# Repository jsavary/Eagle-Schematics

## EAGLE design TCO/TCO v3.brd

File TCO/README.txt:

/************/
*  TCO v1    *
/************/

for roco solenoide turnout with DCC input voltage

/************/
*  TCO v2    *
/************/

some new idea

/************/
*  TCO v3    *
/************/

for Xpressnet tco with arduino
see more at : https://github.com/nzin/xpressnet_arduino

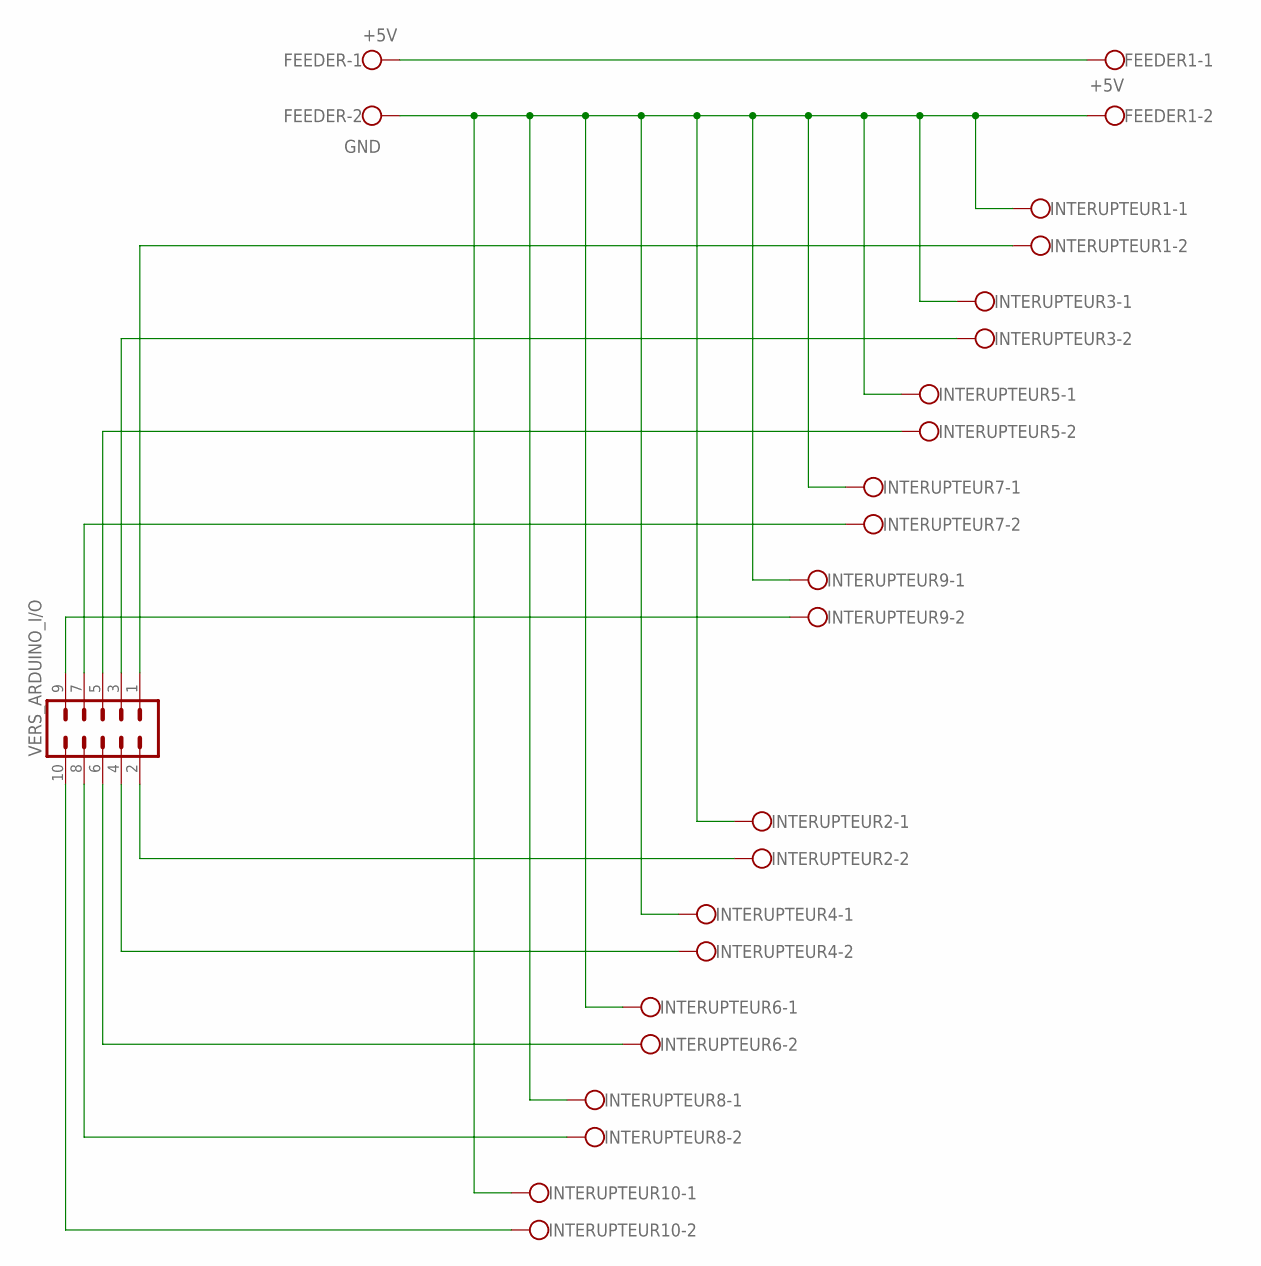
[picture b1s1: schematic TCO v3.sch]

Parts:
FEEDER, FEEDER1: W237-102
INTERUPTEUR1, INTERUPTEUR2, INTERUPTEUR3, INTERUPTEUR4, INTERUPTEUR5, INTERUPTEUR6, INTERUPTEUR7, INTERUPTEUR8, INTERUPTEUR9, INTERUPTEUR10: W237-102
VERS_ARDUINO_I/O: MA05-2

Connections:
unnamed: FEEDER.1, FEEDER1.1
unnamed: INTERUPTEUR1.2, VERS_ARDUINO_I/O.1
unnamed: INTERUPTEUR3.2, VERS_ARDUINO_I/O.3
unnamed: INTERUPTEUR5.2, VERS_ARDUINO_I/O.5
unnamed: INTERUPTEUR7.2, VERS_ARDUINO_I/O.7
unnamed: INTERUPTEUR9.2, VERS_ARDUINO_I/O.9
unnamed: INTERUPTEUR2.2, VERS_ARDUINO_I/O.2
unnamed: INTERUPTEUR4.2, VERS_ARDUINO_I/O.4
unnamed: INTERUPTEUR6.2, VERS_ARDUINO_I/O.6
unnamed: INTERUPTEUR8.2, VERS_ARDUINO_I/O.8
unnamed: INTERUPTEUR10.2, VERS_ARDUINO_I/O.10
unnamed: FEEDER.2, FEEDER1.2, INTERUPTEUR1.1, INTERUPTEUR2.1, INTERUPTEUR3.1, INTERUPTEUR4.1, INTERUPTEUR5.1, INTERUPTEUR6.1, INTERUPTEUR7.1, INTERUPTEUR8.1, INTERUPTEUR9.1, INTERUPTEUR10.1

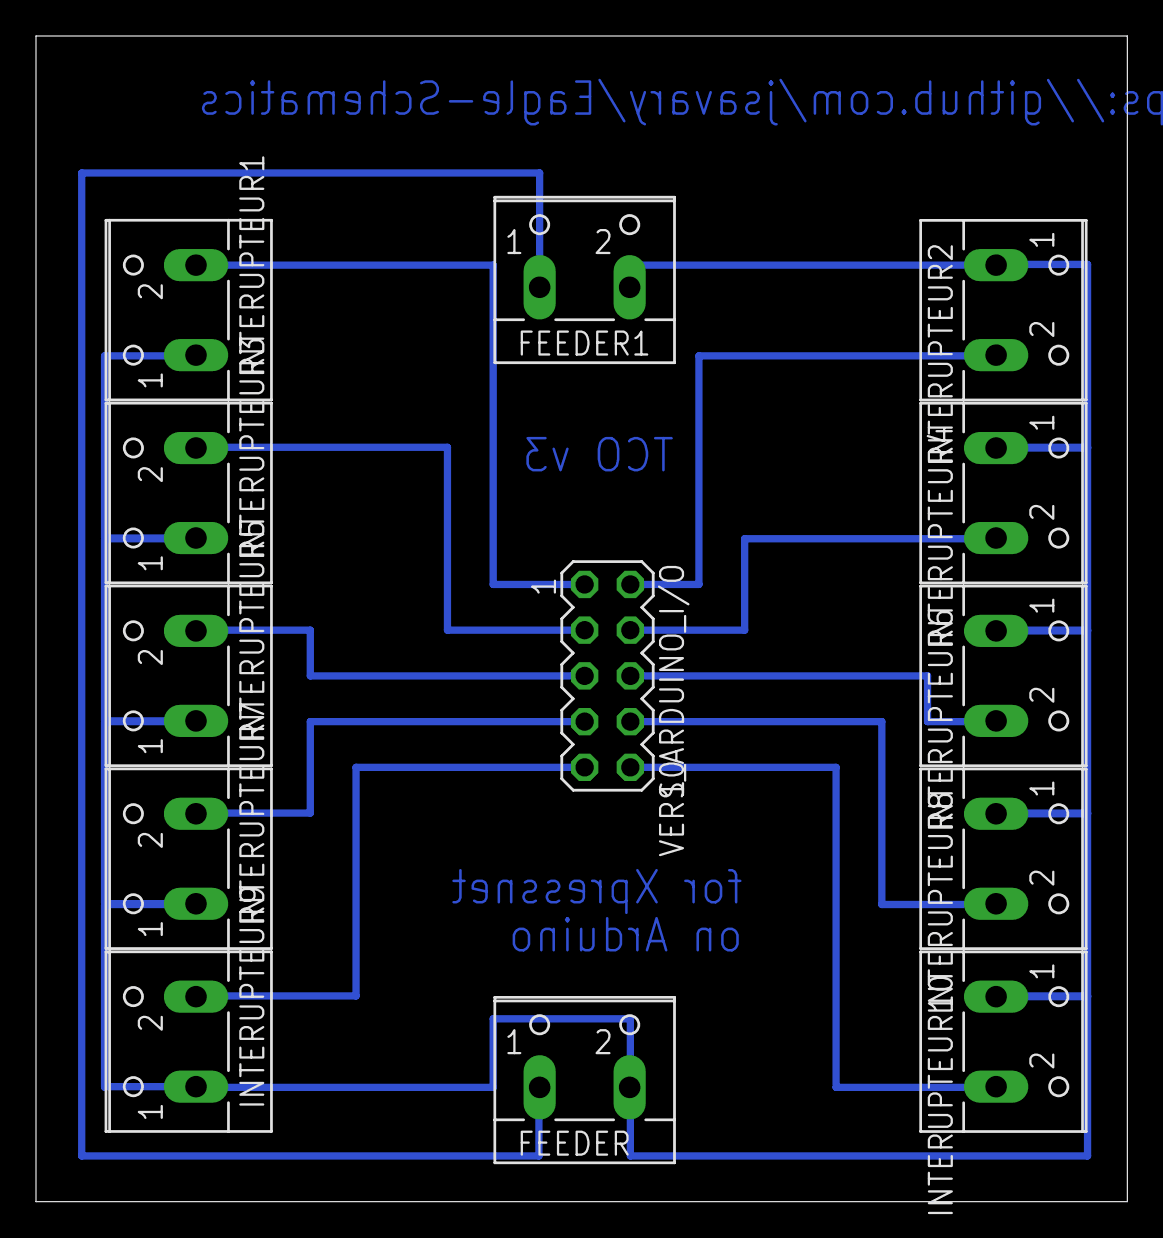
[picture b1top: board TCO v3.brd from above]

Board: 2 copper layers, 60.6 x 64.8 mm, 13 parts (0 on the bottom side), 12 nets.

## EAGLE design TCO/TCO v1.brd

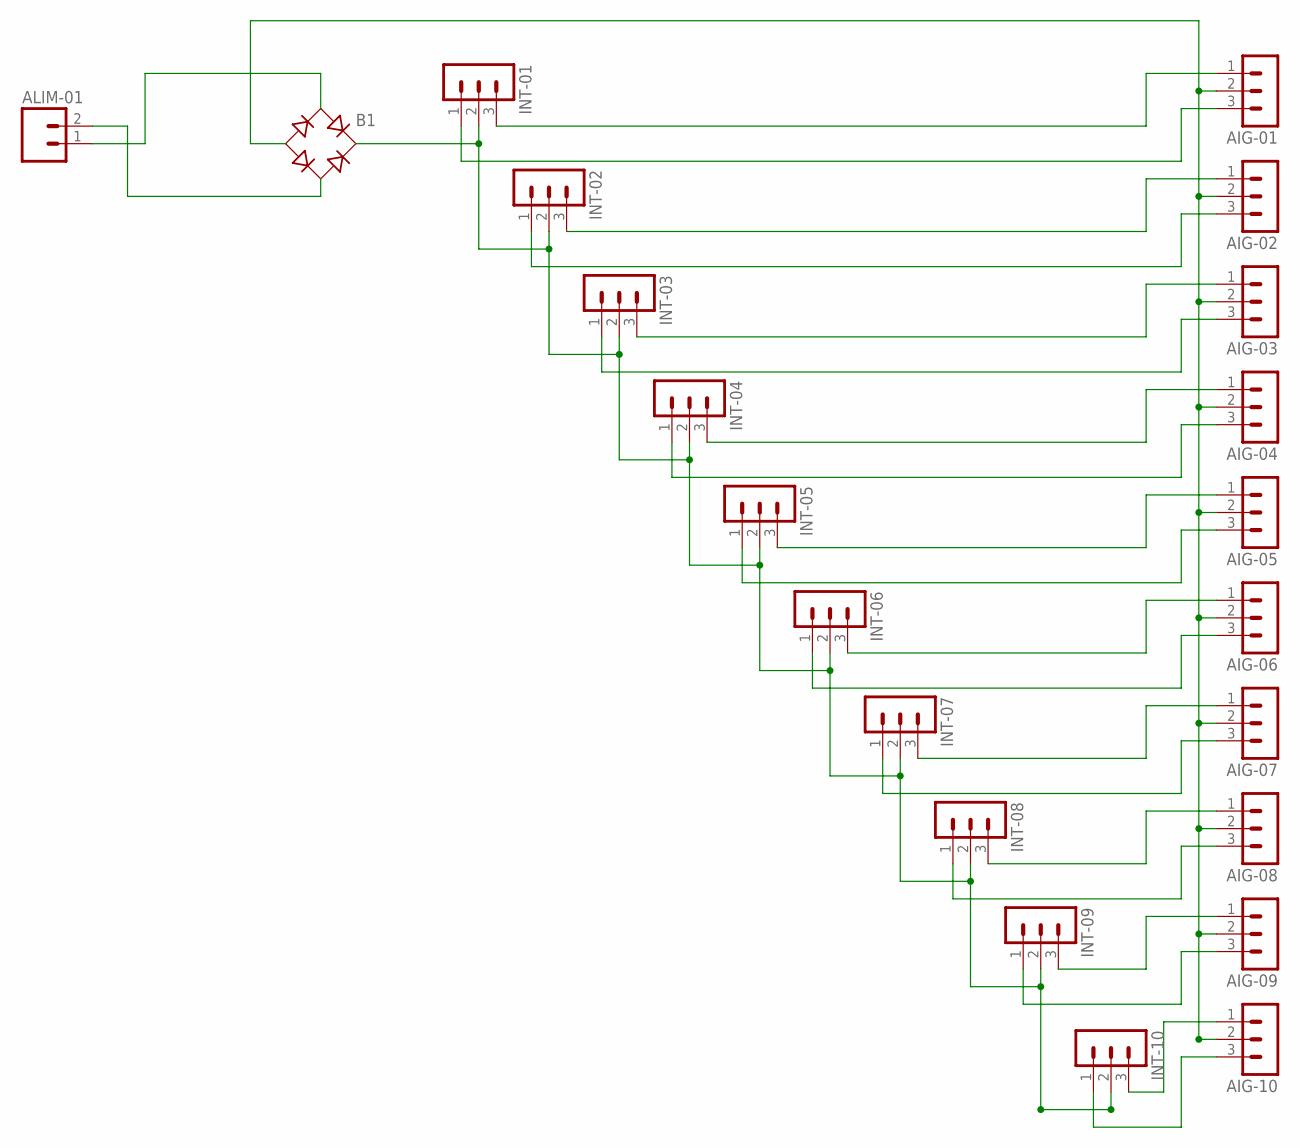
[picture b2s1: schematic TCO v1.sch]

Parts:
AIG-01, AIG-02, AIG-03, AIG-04, AIG-05, AIG-06, AIG-07, AIG-08, AIG-09, AIG-10: MA03-1
ALIM-01: M02; 02P
B1: B-DIL
INT-01, INT-02, INT-03, INT-04, INT-05, INT-06, INT-07, INT-08, INT-09, INT-10: MA03-1

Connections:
unnamed: ALIM-01.1, B1.AC1
unnamed: AIG-01.2, AIG-02.2, AIG-03.2, AIG-04.2, AIG-05.2, AIG-06.2, AIG-07.2, AIG-08.2, AIG-09.2, AIG-10.2, B1.-
unnamed: AIG-01.3, INT-01.1
unnamed: B1.+, INT-01.2, INT-02.2, INT-03.2, INT-04.2, INT-05.2, INT-06.2, INT-07.2, INT-08.2, INT-09.2, INT-10.2
unnamed: AIG-01.1, INT-01.3
unnamed: AIG-02.3, INT-02.1
unnamed: AIG-02.1, INT-02.3
unnamed: AIG-03.3, INT-03.1
unnamed: AIG-03.1, INT-03.3
unnamed: AIG-04.3, INT-04.1
unnamed: AIG-04.1, INT-04.3
unnamed: AIG-05.1, INT-05.3
unnamed: AIG-05.3, INT-05.1
unnamed: AIG-06.1, INT-06.3
unnamed: AIG-06.3, INT-06.1
unnamed: AIG-07.1, INT-07.3
unnamed: AIG-07.3, INT-07.1
unnamed: AIG-08.1, INT-08.3
unnamed: AIG-08.3, INT-08.1
unnamed: AIG-09.1, INT-09.3
unnamed: AIG-09.3, INT-09.1
unnamed: AIG-10.1, INT-10.3
unnamed: AIG-10.3, INT-10.1
unnamed: ALIM-01.2, B1.AC2

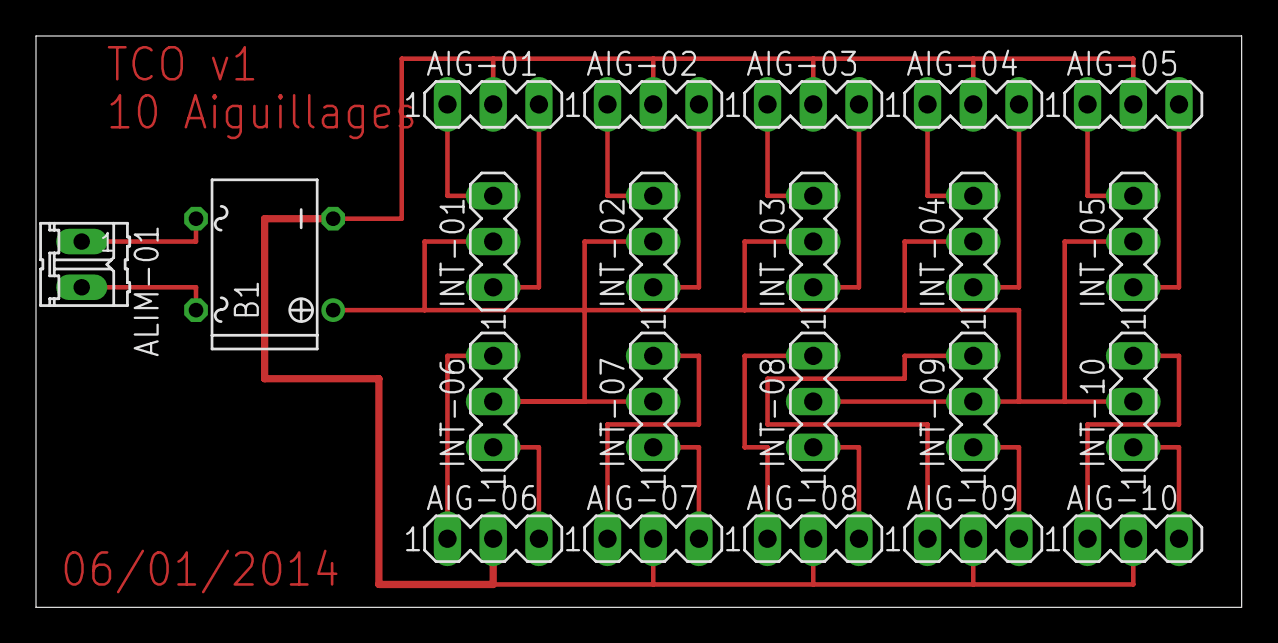
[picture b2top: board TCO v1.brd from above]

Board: 2 copper layers, 67.0 x 31.7 mm, 22 parts (0 on the bottom side), 24 nets.

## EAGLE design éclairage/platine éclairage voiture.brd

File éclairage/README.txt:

/**********************/
* Light cabine for DCC *
/**********************/

This is Made for light into the cabine of trains.

enjoy!

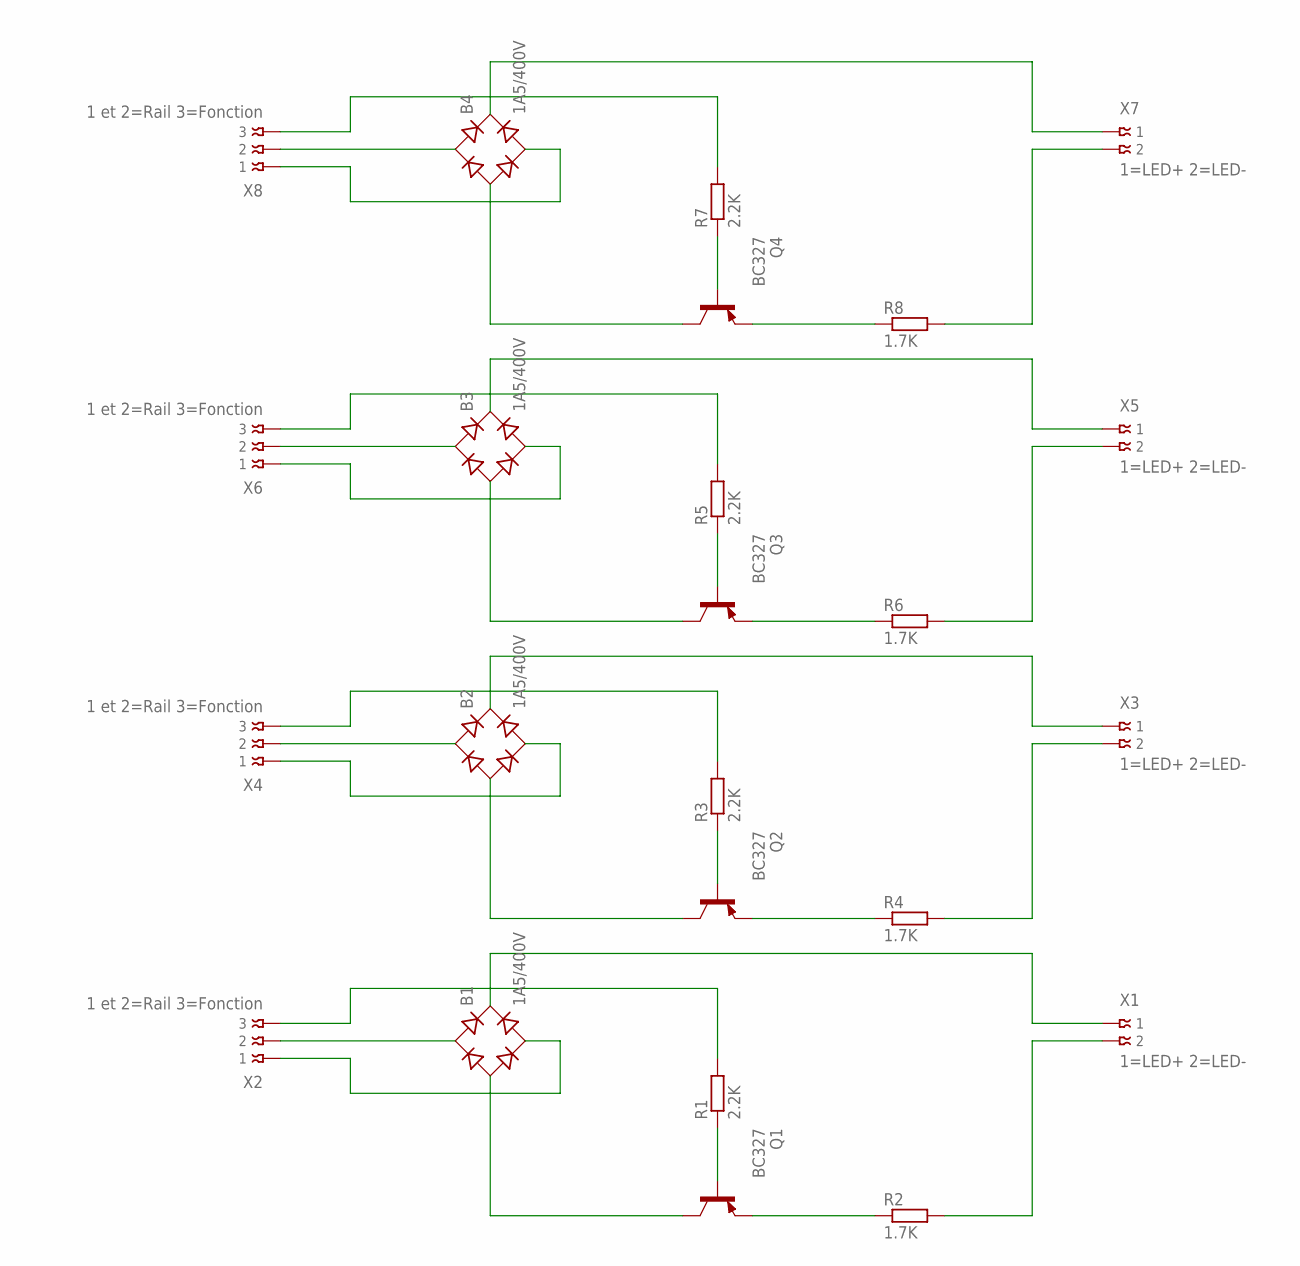
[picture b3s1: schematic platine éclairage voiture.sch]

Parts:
B1, B2, B3, B4: 1A5/400V; RB1A
Q1, Q2, Q3, Q4: BC327; TO92-EBC
R1, R3, R5, R7: 2.2K; 0207/10
R2, R4, R6, R8: 1.7K; 0207/10
X1, X3, X5, X7: 1=LED+ 2=LED-; 009176002
X2, X4, X6, X8: 1 et 2=Rail 3=Fonction; 009176003

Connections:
unnamed: B1.-, Q1.C
unnamed: Q1.B, R1.1
unnamed: R1.2, X2.3
unnamed: Q1.E, R2.1
unnamed: R2.2, X1.2
unnamed: B1.+, X1.1
unnamed: B1.AC1, X2.2
unnamed: B1.AC2, X2.1
unnamed: B2.-, Q2.C
unnamed: Q2.B, R3.1
unnamed: R3.2, X4.3
unnamed: Q2.E, R4.1
unnamed: R4.2, X3.2
unnamed: B2.+, X3.1
unnamed: B2.AC1, X4.2
unnamed: B2.AC2, X4.1
unnamed: B3.-, Q3.C
unnamed: Q3.B, R5.1
unnamed: R5.2, X6.3
unnamed: Q3.E, R6.1
unnamed: R6.2, X5.2
unnamed: B3.+, X5.1
unnamed: B3.AC2, X6.1
unnamed: B3.AC1, X6.2
unnamed: B4.-, Q4.C
unnamed: Q4.B, R7.1
unnamed: R7.2, X8.3
unnamed: Q4.E, R8.1
unnamed: R8.2, X7.2
unnamed: B4.+, X7.1
unnamed: B4.AC2, X8.1
unnamed: B4.AC1, X8.2

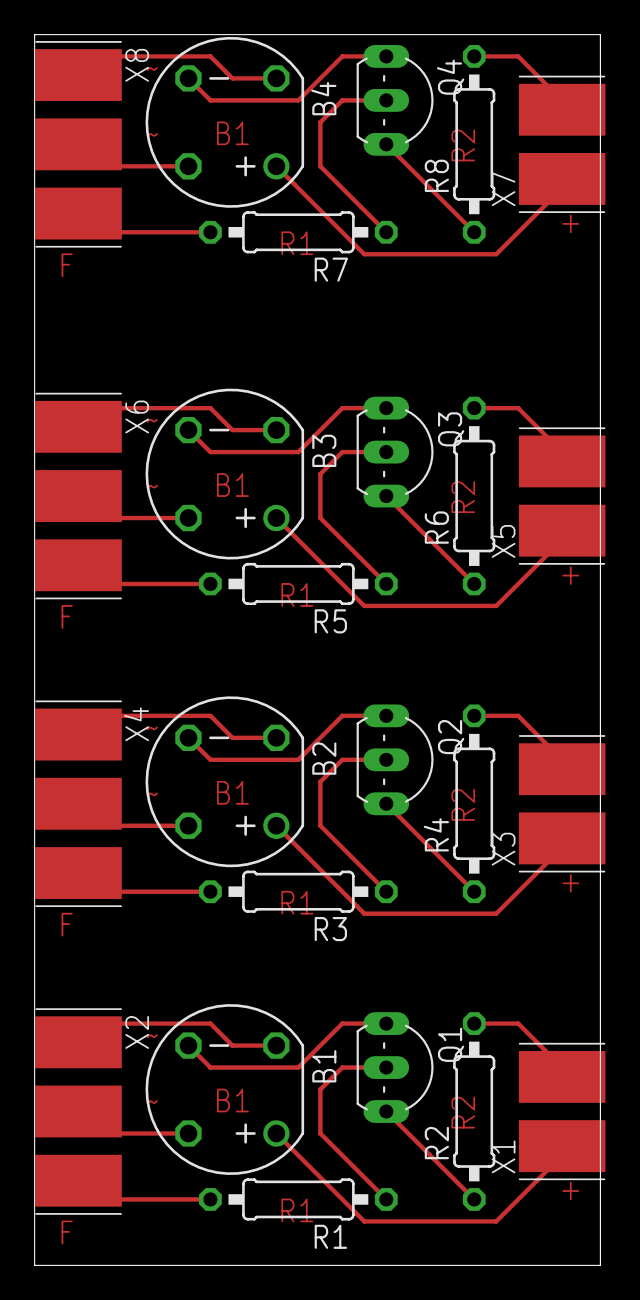
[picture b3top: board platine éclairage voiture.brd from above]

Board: 2 copper layers, 32.7 x 71.1 mm, 24 parts (0 on the bottom side), 32 nets.

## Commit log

2015-02-11 :circus_tent: Added .gitattributes & .gitignore files
2015-02-11 TCO v1
2015-02-11 TCO v2
2015-02-11 Alimentation rail Geoline
2015-02-11 eclairage
2015-02-11 Alimentation
2015-02-11 move
2015-02-11 éclairage
2015-02-11 delete
2015-02-12 add description on board
2015-02-16 update
    optimisation de mmontage
